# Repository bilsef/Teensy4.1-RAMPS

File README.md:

# Teensy4.1-RAMPS
 A Teensy 4.1 to RAMPS adapter board

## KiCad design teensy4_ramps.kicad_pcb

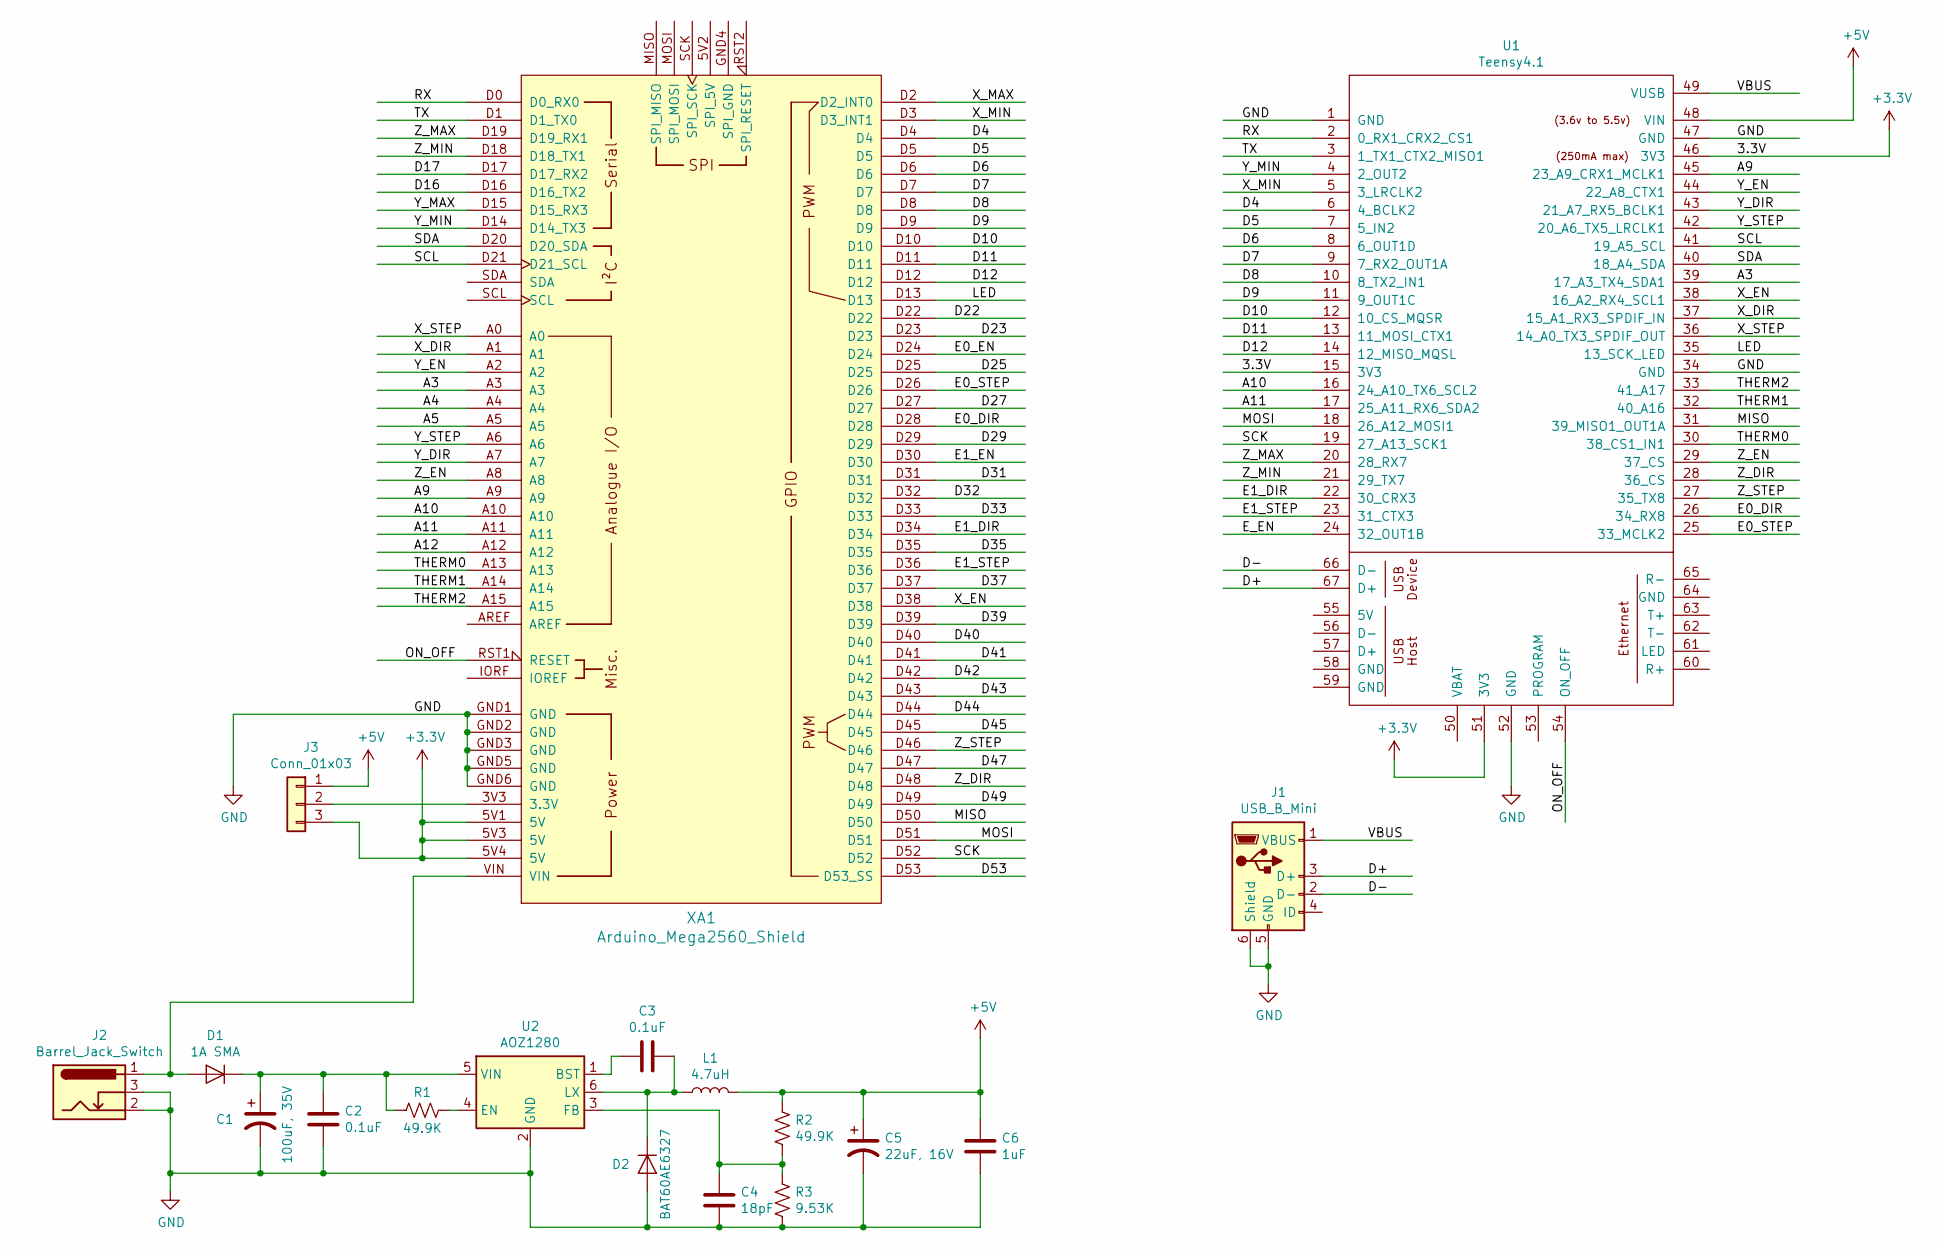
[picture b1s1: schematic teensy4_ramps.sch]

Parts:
C1: 100uF, 35V; C_Elec_6.3x7.7
C2, C3: 0.1uF; C_0402_1005Metric
C4: 18pF; C_0402_1005Metric
C5: 22uF, 16V; CP_Elec_4x5.3
C6: 1uF; C_0402_1005Metric
D1: 1A SMA; D_SMA
D2: BAT60AE6327; D_SOD-323
J1: USB_B_Mini; USB_Mini-B_Lumberg_2486_01_Horizontal
J2: Barrel_Jack_Switch; BarrelJack_Horizontal
J3: Conn_01x03; PinHeader_1x03_P2.54mm_Vertical
L1: 4.7uH; L_Taiyo-Yuden_NR-50xx
R1, R2: 49.9K; R_0402_1005Metric
R3: 9.53K; R_0402_1005Metric
U1: Teensy4.1; Teensy41
U2: AOZ1280; SOT-23-6
XA1: Arduino_Mega2560_Shield

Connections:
+3V3: J3.3, U1.15 (3V3), U1.46 (3V3), U1.51 (3V3), XA1.5V1 (5V), XA1.5V3 (5V), XA1.5V4 (5V)
+5V: C5.1, C6.1, J3.1, L1.2, R2.1, U1.48 (VIN)
/A3: U1.39 (17_A3_TX4_SDA1), XA1.A3
/A4: XA1.A4
/A5: XA1.A5
/A9: U1.45 (23_A9_CRX1_MCLK1), XA1.A9
/A10: U1.16 (24_A10_TX6_SCL2), XA1.A10
/A11: U1.17 (25_A11_RX6_SDA2), XA1.A11
/A12: XA1.A12
/D4: U1.6 (4_BCLK2), XA1.D4
/D5: U1.7 (5_IN2), XA1.D5
/D6: U1.8 (6_OUT1D), XA1.D6
/D7: U1.9 (7_RX2_OUT1A), XA1.D7
/D8: U1.10 (8_TX2_IN1), XA1.D8
/D9: U1.11 (9_OUT1C), XA1.D9
/D10: U1.12 (10_CS_MQSR), XA1.D10
/D11: U1.13 (11_MOSI_CTX1), XA1.D11
/D12: U1.14 (12_MISO_MQSL), XA1.D12
/D16: XA1.D16 (D16_TX2)
/D17: XA1.D17 (D17_RX2)
/D22: XA1.D22
/D23: XA1.D23
/D25: XA1.D25
/D27: XA1.D27
/D29: XA1.D29
/D31: XA1.D31
/D32: XA1.D32
/D33: XA1.D33
/D35: XA1.D35
/D37: XA1.D37
/D39: XA1.D39
/D40: XA1.D40
/D41: XA1.D41
/D42: XA1.D42
/D43: XA1.D43
/D44: XA1.D44
/D45: XA1.D45
/D47: XA1.D47
/D49: XA1.D49
/D53: XA1.D53 (D53_SS)
/D+: J1.3 (D+), U1.67 (D+)
/D-: J1.2 (D-), U1.66 (D-)
/E0_DIR: U1.26 (34_RX8), XA1.D28
/E0_EN: XA1.D24
/E0_STEP: U1.25 (33_MCLK2), XA1.D26
/E1_DIR: U1.22 (30_CRX3), XA1.D34
/E1_EN: XA1.D30
/E1_STEP: U1.23 (31_CTX3), XA1.D36
/E_EN: U1.24 (32_OUT1B)
/LED: U1.35 (13_SCK_LED), XA1.D13
/MISO: U1.31 (39_MISO1_OUT1A), XA1.D50
/MOSI: U1.18 (26_A12_MOSI1), XA1.D51
/ON_OFF: U1.54 (ON_OFF), XA1.RST1 (RESET)
/RX: U1.2 (0_RX1_CRX2_CS1), XA1.D0 (D0_RX0)
/SCK: U1.19 (27_A13_SCK1), XA1.D52
/SCL: U1.41 (19_A5_SCL), XA1.D21 (D21_SCL)
/SDA: U1.40 (18_A4_SDA), XA1.D20 (D20_SDA)
/THERM0: U1.30 (38_CS1_IN1), XA1.A13
/THERM1: U1.32 (40_A16), XA1.A14
/THERM2: U1.33 (41_A17), XA1.A15
/TX: U1.3 (1_TX1_CTX2_MISO1), XA1.D1 (D1_TX0)
/VBUS: J1.1 (VBUS), U1.49 (VUSB)
/X_DIR: U1.37 (15_A1_RX3_SPDIF_IN), XA1.A1
/X_EN: U1.38 (16_A2_RX4_SCL1), XA1.D38
/X_MAX: XA1.D2 (D2_INT0)
/X_MIN: U1.5 (3_LRCLK2), XA1.D3 (D3_INT1)
/X_STEP: U1.36 (14_A0_TX3_SPDIF_OUT), XA1.A0
/Y_DIR: U1.43 (21_A7_RX5_BCLK1), XA1.A7
/Y_EN: U1.44 (22_A8_CTX1), XA1.A2
/Y_MAX: XA1.D15 (D15_RX3)
/Y_MIN: U1.4 (2_OUT2), XA1.D14 (D14_TX3)
/Y_STEP: U1.42 (20_A6_TX5_LRCLK1), XA1.A6
/Z_DIR: U1.28 (36_CS), XA1.D48
/Z_EN: U1.29 (37_CS), XA1.A8
/Z_MAX: U1.20 (28_RX7), XA1.D19 (D19_RX1)
/Z_MIN: U1.21 (29_TX7), XA1.D18 (D18_TX1)
/Z_STEP: U1.27 (35_TX8), XA1.D46
GND: C1.2, C2.2, C4.2, C5.2, C6.2, D2.2 (A), J1.5 (GND), J1.6 (Shield), J2.2, J2.3, R3.2, U1.1 (GND), U1.34 (GND), U1.47 (GND), U1.52 (GND), U2.2 (GND), XA1.GND1 (GND), XA1.GND2 (GND), XA1.GND3 (GND), XA1.GND5 (GND), XA1.GND6 (GND)
unnamed: C1.1, C2.1, D1.1 (K), R1.2, U2.5 (VIN)
unnamed: C3.1, D2.1 (K), L1.1, U2.6 (LX)
unnamed: C3.2, U2.1 (BST)
unnamed: C4.1, R2.2, R3.1, U2.3 (FB)
unnamed: D1.2 (A), J2.1, XA1.VIN
unnamed: J3.2, XA1.3V3 (3.3V)
unnamed: R1.1, U2.4 (EN)

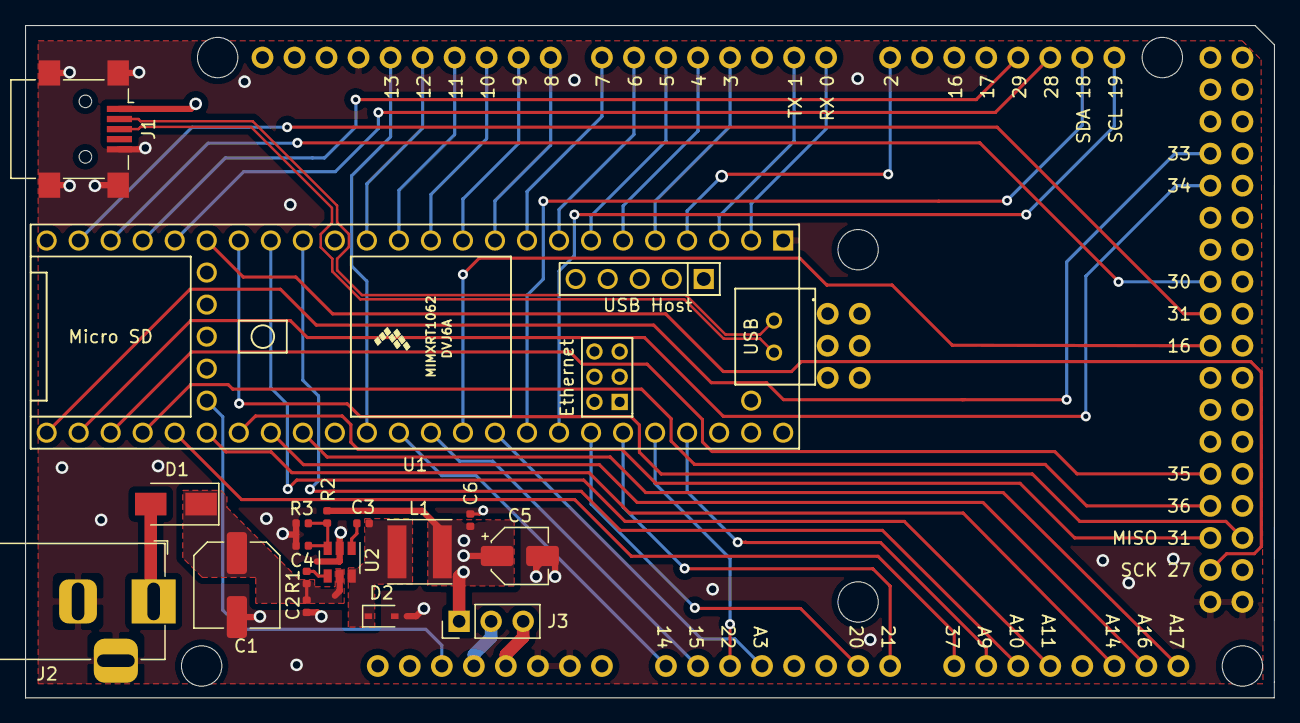
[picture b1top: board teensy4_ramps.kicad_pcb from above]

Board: 4 copper layers, 99.1 x 53.3 mm, 18 parts (0 on the bottom side), 55 nets.

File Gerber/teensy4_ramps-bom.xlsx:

Comment | Desisgnator | Footprint | LCSSC Part # | Description
100uF, 35V | C1 | C_Elec_6.3x7.7 | C134792 | 100uF ±20% 35V SMD,6.3x7.7mm
100nF | C2, C3 | C_0402 | C1525 | MULTILAYER CERAMIC CAPACITORS MLCC - SMD/SMT 100NF 16V 0402 ROHS
18pF | C4 | C_0402 | C1549 | MULTILAYER CERAMIC CAPACITORS MLCC - SMD/SMT 18PF 50V 0402 ROHS
22uF, 16V | C5 | CP_Elec_4x5.3 | C134793 | 22UF ±20% 16V SMD,4X5.3MM ALUMINUM ELECTROLYTIC CAPACITORS - SMD ROHS
1uF | C6 | C_0402 | C52923 | MULTILAYER CERAMIC CAPACITORS MLCC - SMD/SMT 1UF 25V 0402 ROHS
1A SMA | D1 | D_SMA | C260338 | 50V 1A 1.1V @ 1A SMA DIODES - GENERAL PURPOSE ROHS
BAT60AE6327 | D2 | D_SOD-323 | C117485 | 10V 3A 370MV @ 1A SOD-323 SCHOTTKY BARRIER DIODES (SBD) ROHS
4.7uH | L1 | L_4.7x5.2 | C477170 | 4.7UH ±20% 3A 46MΩ SMD,4.7X5.2X3.0MM INDUCTORS (SMD) ROHS
49.9K | R1, R2 | R_0402 | C25897 | CHIP RESISTOR - SURFACE MOUNT 49.9KOHMS ±1% 1/16W 0402 ROHS
9.53K | R3 | R_0402 | C96273 | CHIP RESISTOR - SURFACE MOUNT 9.53KOHMS ±1% 1/16W 0402 ROHS
AOZ1280CI | U2 | SOT-23-6 | C41240 | DC-DC CONVERTERS STEP-DOWN ADJUSTABLE 1 3V 26V 0.8V 1.2A SOT-23-6 ROHS

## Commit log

2020-10-16 Inital commit
